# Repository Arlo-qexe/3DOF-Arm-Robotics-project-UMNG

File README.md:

# Brazo Robótico 3DOF — Proyecto UMNG

Diseño, construcción y control de un brazo robótico de 3 grados de libertad (3-DOF) capaz de ejecutar tareas de manipulación autónoma. El proyecto abarca desde el diseño CAD y simulación hasta la implementación física completa: electrónica, firmware en ESP32, interfaz de control y planificación de trayectorias.

> **Aplicación demo:** clasificación y transporte autónomo de pelotas de ping pong entre posiciones predefinidas.

---

## Robot físico

| Vista lateral | Vista frontal (laboratorio) |
|---|---|
|  |  |

---

## 🎯 Objetivos

### Objetivo general
Diseñar, construir y controlar un brazo robótico de 3 DOF capaz de posicionar su efector final mediante cinemática directa e inversa, y ejecutar tareas de manipulación autónoma con trayectorias planificadas.

### Objetivos específicos
- Diseñar la estructura mecánica completa (CAD + impresión 3D + corte láser)
- Diseñar e implementar el circuito electrónico de control (PCB personalizada)
- Modelar matemáticamente el sistema (cinemática directa e inversa, Jacobiano)
- Implementar firmware en ESP32 para control de 3 motores DC con encoders
- Desarrollar una interfaz gráfica de control y monitoreo en Python
- Implementar un simulador de planificación de trayectorias
- Integrar simulación en ROS2/Gazebo con modelo URDF
- Ejecutar la tarea de clasificación de pelotas de ping pong

---

## 📂 Estructura del repositorio

```
├── Act/                          → Actas de reuniones del proyecto
├── Documentos/                   → Análisis de contexto y documentación
├── Hardware/
│   ├── CAD/                      → Diseños CAD (SolidWorks, DXF)
│   ├── PCB/                      → PCB personalizada (ESP32 + BTS7960 + 3 motores DC)
│   ├── Gripper/                  → Modelo STL del gripper
│   ├── STLs/ y STLS/             → Piezas impresas en 3D
│   └── Engranaje de Eslabon*.png → Renders de engranajes
├── Resources/
│   ├── VIDEOS/                   → Videos de pruebas y resultado final
│   ├── Trayectorias/             → CSVs de trayectorias (articular y cartesiana)
│   ├── Datos caracterizacion Motores/ → Datos encoder de los 3 motores
│   └── *.png / *.jpg             → Imágenes del proyecto
├── Software/
│   ├── brazo_integrado (4).py    → Interfaz principal de control + planificador
│   ├── abdul3dof_gui.py          → GUI de control de posición
│   ├── Gazebo/                   → Simulación en Gazebo (URDF, workspace ROS2)
│   ├── URDF/                     → Modelo URDF del brazo
│   ├── brazo_robot/              → Paquete ROS2 del robot
│   └── ws_manip/                 → Workspace de manipulación ROS2
├── README.md
└── LICENSE
```

---

## 🔧 Hardware

### Diseño mecánico (SolidWorks)

El brazo fue diseñado completamente en SolidWorks e impreso en 3D. Incluye tres eslabones, base giratoria, gripper y bandeja dispensadora de pelotas.

| Ensamblaje completo | Ensamblaje v1 |
|---|---|
|  |  |

| Dimensiones dispensador | Bandeja ping pong (impresa) |
|---|---|
|  |  |

### Electrónica — PCB personalizada

Se diseñó e implementó una PCB a medida con:
- **ESP32** como microcontrolador principal
- **BTS7960** (×3) para control de motores DC con PWM
- Conectores de encoder para los 3 motores
- Fabricada en Bogotá (2026-04-10)

El esquemático completo está disponible en: [`Resources/Esquemático – ESP32 + BTS7960 + 3 Motores DC.pdf`](Resources/Esquemático%20–%20ESP32%20+%20BTS7960%20+%203%20Motores%20DC.pdf)

---

## 💻 Software

### Interfaz de control de posición

Interfaz gráfica en Python (`abdul3dof_gui.py`) con conexión serial al ESP32:

- Control independiente de 3 motores (M1 Base, M2 Hombro, M3 Codo)
- Visualización 3D en tiempo real de cinemática directa
- Gráfica de posición articular en tiempo real
- Cálculo y ejecución de cinemática inversa
- Reset de posición con un clic

### Simulador de planificación de trayectorias

El simulador integrado (`brazo_integrado (4).py`) permite planificar y animar trayectorias completas:

- Editor de waypoints (XYZ o articular)
- 3 modos de interpolación: **articular (curva)**, **cartesiana (recta)**, **control cinemático (Jacobiano)**
- Visualización 3D animada de la trayectoria del efector final
- Gráficas: posición articular, velocidad, aceleración y posición XYZ del EE
- Importación de trayectorias desde CSV
- Gripper integrado en la simulación
- Resumen automático: waypoints, tramos, tiempo total

| Planificador de trayectorias (ping pong articular) | Ángulos enviados / control real |
|---|---|
|  |  |

**Trayectoria ping pong:** 22 waypoints, 21 tramos, tiempo total ≈ 31.5 s, gripper 40 mm de apertura.

### Simulación ROS2 / Gazebo

Simulación completa con modelo URDF en Gazebo y visualización en RViz:

| RViz — modelo 3D | Gazebo + interfaz Python |
|---|---|
|  |  |

### Cinemática inversa interactiva

Archivo HTML autocontenido (`Resources/cinematica_inversa_interactiva.html`) para explorar visualmente la cinemática inversa del brazo en el navegador, sin instalación adicional.

---

## 🏓 Aplicación: clasificación de pelotas de ping pong

El robot ejecuta una secuencia autónoma de pick & place: recoge pelotas del dispensador y las deposita en posiciones predefinidas de una bandeja receptora.

- **Dispensador:** bandeja 3D-impresa con ranuras para pelotas de colores
- **Gripper:** pinza impresa en 3D (apertura 40 mm)
- **Trayectoria:** planificada con el simulador y cargada via CSV al firmware
- **Ejecución:** ~31.5 s por ciclo completo (3 pelotas)

**Video — prueba final:**
<video src="https://raw.githubusercontent.com/Arlo-qexe/3DOF-Arm-Robotics-project-UMNG/main/Resources/VIDEOS/video_final.mp4" controls width="720"></video>
Más videos de prueba en [`Resources/VIDEOS/`](Resources/VIDEOS/)

---

## 📊 Caracterización de motores

Se midieron y registraron curvas de velocidad y posición (encoder) para los 3 motores bajo distintas condiciones:

```
Resources/Datos caracterizacion Motores/
├── M1_Encoder_data_210.csv
├── M2_Encoder_data_rads_210.csv
├── M3_Encoder_data_rads_270.csv
└── ...
```

---

## 👩‍💻 Autores

Proyecto desarrollado por estudiantes de Ingeniería — **Universidad Militar Nueva Granada (UMNG)**:

- **Carlos Andrés Quintero Forero**
- **Salim Abdul Fayad Diaz**
- **Natalia Almanza**

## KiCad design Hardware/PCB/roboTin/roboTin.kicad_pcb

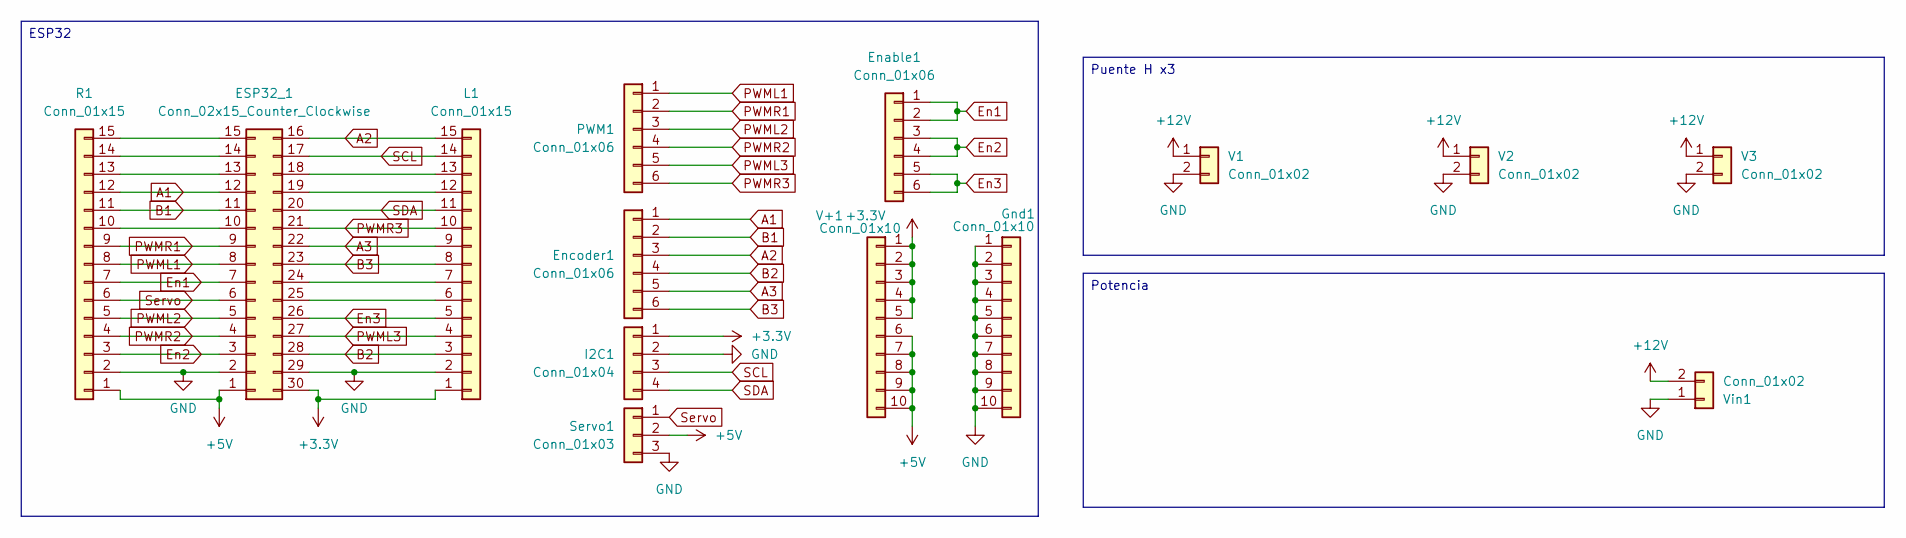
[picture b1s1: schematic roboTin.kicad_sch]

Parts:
ESP32_1: Conn_02x15_Counter_Clockwise; ESP_Test
Enable1: Conn_01x06; PinHeader_1x06_P2.54mm_Vertical
Encoder1: Conn_01x06; PinHeader_1x06_P2.54mm_Vertical
Gnd1: Conn_01x10; PinHeader_1x10_P2.54mm_Vertical
I2C1: Conn_01x04; PinHeader_1x04_P2.54mm_Vertical
L1: Conn_01x15; PinHeader_1x15_P2.54mm_Vertical
PWM1: Conn_01x06; PinHeader_1x06_P2.54mm_Vertical
R1: Conn_01x15; PinHeader_1x15_P2.54mm_Vertical
Servo1: Conn_01x03; PinHeader_1x03_P2.54mm_Vertical
V1, V2, V3: Conn_01x02; PhoenixContact_MSTBA_2,5_2-G-5,08_1x02_P5.08mm_Horizontal
V+1: Conn_01x10; PinHeader_1x10_P2.54mm_Vertical
Vin1: Conn_01x02; PhoenixContact_MSTBA_2,5_2-G-5,08_1x02_P5.08mm_Horizontal

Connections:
+3.3V: ESP32_1.30, I2C1.1, L1.1, V+1.1, V+1.2, V+1.3, V+1.4, V+1.5
+5V: ESP32_1.1, R1.1, Servo1.2, V+1.6, V+1.7, V+1.8, V+1.9, V+1.10
+12V: V1.1, V2.1, V3.1, Vin1.2
A1: ESP32_1.12, Encoder1.1, R1.12
A2: ESP32_1.16, Encoder1.3, L1.15
A3: ESP32_1.22, Encoder1.5, L1.9
B1: ESP32_1.11, Encoder1.2, R1.11
B2: ESP32_1.28, Encoder1.4, L1.3
B3: ESP32_1.23, Encoder1.6, L1.8
En1: ESP32_1.7, Enable1.1, Enable1.2, R1.7
En2: ESP32_1.3, Enable1.3, Enable1.4, R1.3
En3: ESP32_1.26, Enable1.5, Enable1.6, L1.5
GND: ESP32_1.2, ESP32_1.29, Gnd1.1, Gnd1.2, Gnd1.3, Gnd1.4, Gnd1.5, Gnd1.6, Gnd1.7, Gnd1.8, Gnd1.9, Gnd1.10, I2C1.2, L1.2, R1.2, Servo1.3, V1.2, V2.2, V3.2, Vin1.1
unnamed: ESP32_1.10, R1.10
unnamed: ESP32_1.13, R1.13
unnamed: ESP32_1.14, R1.14
unnamed: ESP32_1.15, R1.15
unnamed: ESP32_1.18, L1.13
unnamed: ESP32_1.19, L1.12
unnamed: ESP32_1.24, L1.7
unnamed: ESP32_1.25, L1.6
PWML1: ESP32_1.8, PWM1.1, R1.8
PWML2: ESP32_1.5, PWM1.3, R1.5
PWML3: ESP32_1.27, L1.4, PWM1.5
PWMR1: ESP32_1.9, PWM1.2, R1.9
PWMR2: ESP32_1.4, PWM1.4, R1.4
PWMR3: ESP32_1.21, L1.10, PWM1.6
SCL: ESP32_1.17, I2C1.3, L1.14
SDA: ESP32_1.20, I2C1.4, L1.11
Servo: ESP32_1.6, R1.6, Servo1.1

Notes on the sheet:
Puente H x3
Potencia
ESP32

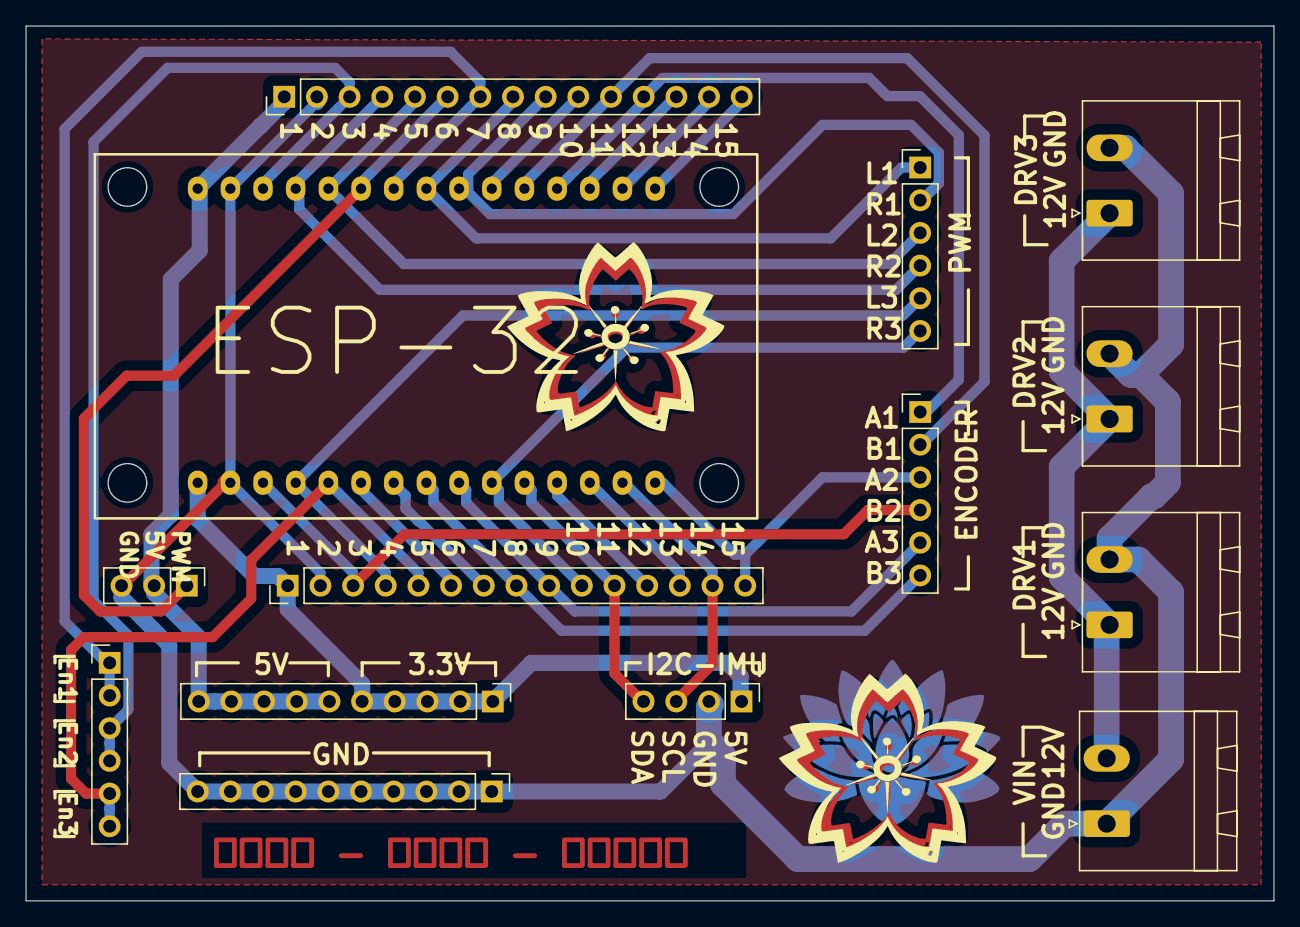
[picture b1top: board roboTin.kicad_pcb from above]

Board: 2 copper layers, 97.0 x 68.0 mm, 14 parts (0 on the bottom side), 30 nets.

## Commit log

2026-03-17 Fix formatting in project title in README
2026-03-17 Actualizacion archivos
2026-03-17 Interfaz python
2026-03-17 CADs
2026-03-18 Actas de trabajo del proyecto
2026-03-20 Imagenes en readme
2026-03-20 Readme
2026-03-25 Diseño PCB para mayor orden de conexiones
2026-03-27 STLs
2026-04-07 Gears
2026-04-21 some more hardware
2026-05-13 ActasII
2026-05-13 Actaaaaaaaaaaaa
2026-05-13 actas
2026-05-26 A lil bit of everything ;p
2026-05-26 some more 📦
2026-05-26 assembly pics
2026-05-26 assembly picture update
2026-05-31 Videos
2026-05-31 Readme update
2026-06-01 Fix video link in README.md
    Updated video source link in README to point directly to the raw file.
